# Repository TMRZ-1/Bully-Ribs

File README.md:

# Bully-Ribs

Here you can find all the files for the Bully-Ribs project.

What could be improved:

- In KiCad I used the nice!nano controller, but I actually built it with a ProMicro RP2040, so the pin labels on the silkscreen are not correct :)))))))

- The PCB doesn’t have a reset button, but luckily the ProMicro RP2040 does.

- The case has the USB cutout a bit too high, so I just trimmed some plastic.

INSPIRATIONS

[Bully](https://github.com/zhol0777/bully-files)

[Lumberjack](https://github.com/peej/lumberjack-keyboard)

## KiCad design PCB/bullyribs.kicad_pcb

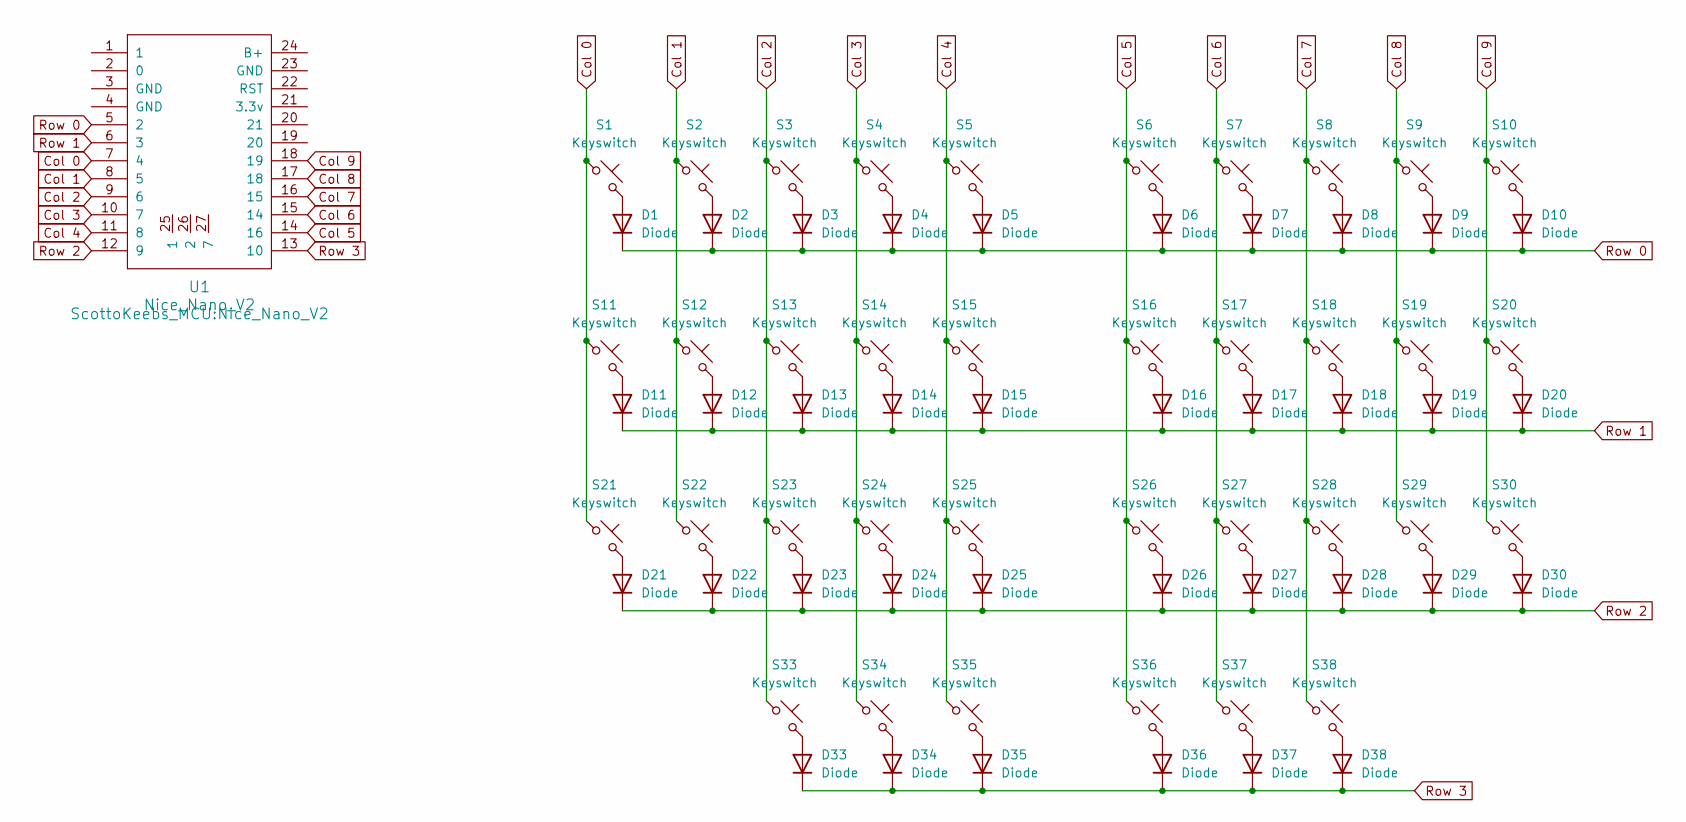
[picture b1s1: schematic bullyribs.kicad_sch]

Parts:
D1, D2, D3, D4, D5, D6, D7, D8, D9, D10, D11, D12, D13, D14, D15, D16, D17, D18, D19, D20, D21, D22, D23, D24, D25, D26, D27, D28, D29, D30, D33, D34, D35, D36, D37, D38: Diode; Diode_SOD-123
S1, S2, S3, S4, S5, S6, S7, S8, S9, S10, S11, S12, S13, S14, S15, S16, S17, S18, S19, S20, S21, S22, S23, S24, S25, S26, S27, S28, S29, S30, S33, S34, S37, S38: Keyswitch; MX_PCB_1.00u
S35, S36: Keyswitch; MX_PCB_1.50u
U1: Nice_Nano_V2

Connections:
Col 0: S1.1, S11.1, S21.1, U1.7 (4)
Col 1: S2.1, S12.1, S22.1, U1.8 (5)
Col 2: S3.1, S13.1, S23.1, S33.1, U1.9 (6)
Col 3: S4.1, S14.1, S24.1, S34.1, U1.10 (7)
Col 4: S5.1, S15.1, S25.1, S35.1, U1.11 (8)
Col 5: S6.1, S16.1, S26.1, S36.1, U1.14 (16)
Col 6: S7.1, S17.1, S27.1, S37.1, U1.15 (14)
Col 7: S8.1, S18.1, S28.1, S38.1, U1.16 (15)
Col 8: S9.1, S19.1, S29.1, U1.17 (18)
Col 9: S10.1, S20.1, S30.1, U1.18 (19)
unnamed: D1.2 (A), S1.2
unnamed: D2.2 (A), S2.2
unnamed: D3.2 (A), S3.2
unnamed: D4.2 (A), S4.2
unnamed: D5.2 (A), S5.2
unnamed: D6.2 (A), S6.2
unnamed: D7.2 (A), S7.2
unnamed: D8.2 (A), S8.2
unnamed: D9.2 (A), S9.2
unnamed: D10.2 (A), S10.2
unnamed: D11.2 (A), S11.2
unnamed: D12.2 (A), S12.2
unnamed: D13.2 (A), S13.2
unnamed: D14.2 (A), S14.2
unnamed: D15.2 (A), S15.2
unnamed: D16.2 (A), S16.2
unnamed: D17.2 (A), S17.2
unnamed: D18.2 (A), S18.2
unnamed: D19.2 (A), S19.2
unnamed: D20.2 (A), S20.2
unnamed: D21.2 (A), S21.2
unnamed: D22.2 (A), S22.2
unnamed: D23.2 (A), S23.2
unnamed: D24.2 (A), S24.2
unnamed: D25.2 (A), S25.2
unnamed: D26.2 (A), S26.2
unnamed: D27.2 (A), S27.2
unnamed: D28.2 (A), S28.2
unnamed: D29.2 (A), S29.2
unnamed: D30.2 (A), S30.2
unnamed: D33.2 (A), S33.2
unnamed: D34.2 (A), S34.2
unnamed: D35.2 (A), S35.2
unnamed: D36.2 (A), S36.2
unnamed: D37.2 (A), S37.2
unnamed: D38.2 (A), S38.2
Row 0: D1.1 (K), D2.1 (K), D3.1 (K), D4.1 (K), D5.1 (K), D6.1 (K), D7.1 (K), D8.1 (K), D9.1 (K), D10.1 (K), U1.5 (2)
Row 1: D11.1 (K), D12.1 (K), D13.1 (K), D14.1 (K), D15.1 (K), D16.1 (K), D17.1 (K), D18.1 (K), D19.1 (K), D20.1 (K), U1.6 (3)
Row 2: D21.1 (K), D22.1 (K), D23.1 (K), D24.1 (K), D25.1 (K), D26.1 (K), D27.1 (K), D28.1 (K), D29.1 (K), D30.1 (K), U1.12 (9)
Row 3: D33.1 (K), D34.1 (K), D35.1 (K), D36.1 (K), D37.1 (K), D38.1 (K), U1.13 (10)

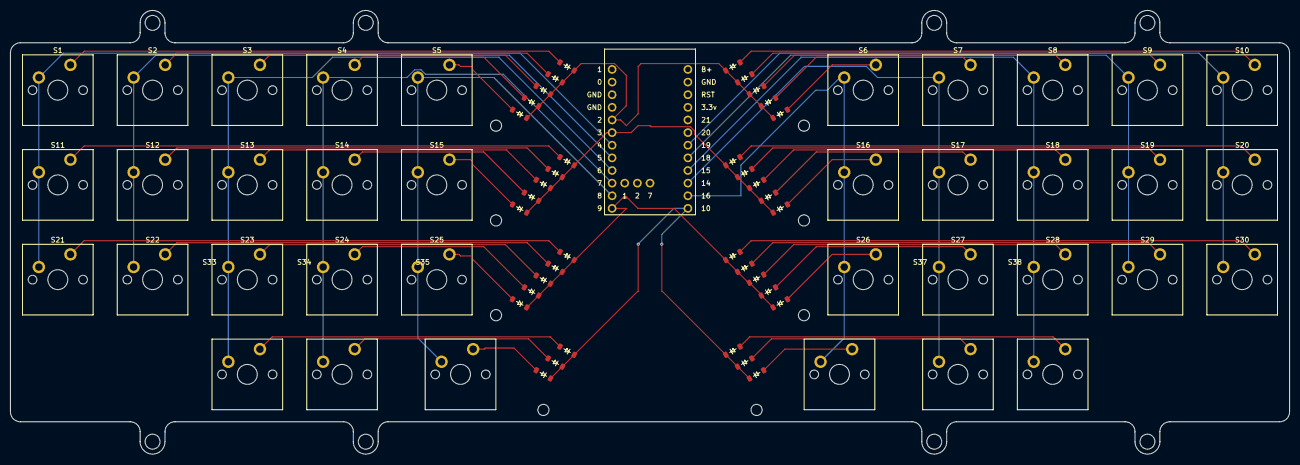
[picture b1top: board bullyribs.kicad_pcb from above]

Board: 2 copper layers, 257.2 x 89.2 mm, 73 parts (0 on the bottom side), 50 nets.
